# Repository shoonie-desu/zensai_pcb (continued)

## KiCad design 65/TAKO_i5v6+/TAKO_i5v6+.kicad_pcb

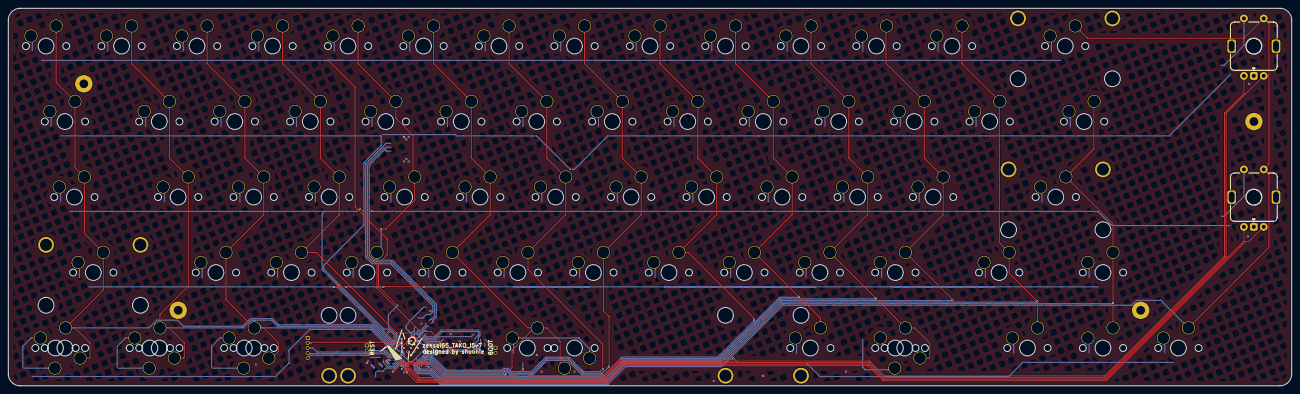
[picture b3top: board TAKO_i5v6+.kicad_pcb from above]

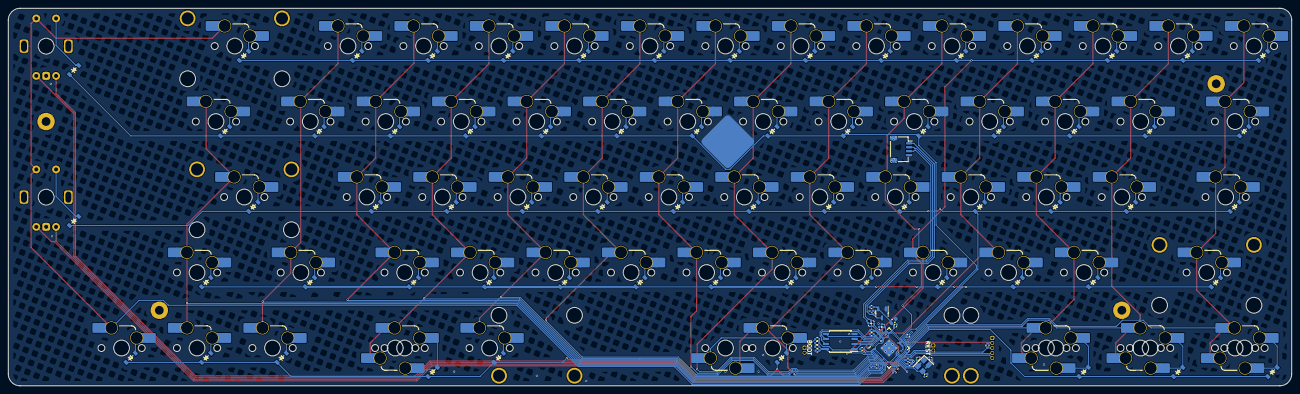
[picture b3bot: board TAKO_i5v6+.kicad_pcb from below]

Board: 2 copper layers, 323.8 x 95.2 mm, 177 parts (163 on the bottom side), 111 nets.

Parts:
C1, C2, C4, C6, C12: 1u; C_0402_1005Metric
C3: 10u; C_0603_1608Metric
C5, C7, C8, C9, C13, C14, C15, C16: 100n; C_0402_1005Metric
C10, C11: 22p; C_0402_1005Metric
D1, D2, D3, D4, D5, D6, D7, D8, D9, D10, D11, D12, D13, D15, D17, D18, D19, D20, D21, D22, D23, D24, D25, D26, D27, D28, D29, D30, D32, D34, D35, D36, D37, D38, D39, D40, D41, D42, D43, D44, D45, D47, D48, D50, D52, D53, D54, D55, D56, D57, D58, D59, D60, D61, D62, D63, D64, D66, D68, D70, D72, D74, D75, D76, D77: D_Small; D_SOD-123_CLEAN
H1, H2, H3, H4: MountingHole_Pad; MountingHole_2.2mm_M2_Pad
H5: info
H7: MountingHole_Pad; MountingHole_6mm_Pad
J1: ZX-SH1.0-4PWT; JST_SH_SM04B-SRSS-TB_1x04-1MP_P1.00mm_Horizontal
J3: Conn_01x05; PinHeader_1x05_P1.27mm_Vertical
R3, R8, R9: 5.1k; R_0402_1005Metric
R4, R5: 27; R_0402_1005Metric
R6, R7: 1k; R_0402_1005Metric
S15, S47, S50: MX_stab; STAB_MX_P_2u
S70: MX_stab; STAB_MX_P_6.25u
S71: MX_stab; STAB_MX_P_7u
SW1, SW2, SW3, SW4, SW5, SW6, SW7, SW8, SW9, SW10, SW11, SW12, SW13, SW15, SW17, SW18, SW19, SW20, SW21, SW22, SW23, SW24, SW25, SW26, SW27, SW28, SW29, SW30, SW34, SW35, SW36, SW37, SW38, SW39, SW40, SW41, SW42, SW43, SW44, SW45, SW47, SW50, SW52, SW53, SW54, SW55, SW56, SW57, SW58, SW59, SW60, SW61, SW62, SW63, SW64, SW65, SW66, SW67, SW68, SW69, SW70, SW71, SW72, SW73, SW74, SW75, SW76, SW77: SW_MX_HS_S; SW_MX_HS_S_CPG151101S11_1u
SW32, SW48: RotaryEncoder_Switch; ROT_Alps_EC11E-Switch
SW78: SW_RESET; PinHeader_1x02_P1.27mm_Vertical
SW79: SW_BOOTSEL; PinHeader_1x02_P1.27mm_Vertical
U1: RP2040; QFN-56-1EP_7x7mm_P0.4mm_EP3.2x3.2mm
U2: XC6206PxxxMR; SOT-23-3
U4: W25Q128JVS; SOIC-8_5.23x5.23mm_P1.27mm
Y1: Crystal_GND24; Crystal_SMD_3225-4Pin_3.2x2.5mm

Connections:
+1V1: C4.1, C5.1, C13.1, U1.23 (DVDD), U1.45 (VREG_VOUT), U1.50 (DVDD)
+3V3: C2.1, C3.1, C6.1, C7.1, C8.1, C9.1, C12.1, C14.1, C15.1, C16.1, J3.2, R3.2, R9.2, U1.1 (IOVDD), U1.10 (IOVDD), U1.22 (IOVDD), U1.33 (IOVDD), U1.42 (IOVDD), U1.43 (ADC_AVDD), U1.44 (VREG_IN), U1.48 (USB_VDD), U1.49 (IOVDD), U2.2 (VO), U4.8 (VCC)
+5V: C1.1, J1.1, U2.3 (VI)
COL0: SW1.2, SW17.2, SW34.2, SW50.2, SW64.2, SW65.1, U1.30 (GPIO19)
COL1: SW2.2, SW18.2, SW35.2, SW66.2, SW67.1, U1.29 (GPIO18)
COL2: SW3.2, SW19.2, SW36.2, SW52.2, SW68.2, SW69.1, U1.28 (GPIO17)
COL3: SW4.2, SW20.2, SW37.2, SW53.2, U1.2 (GPIO0)
COL4: SW5.2, SW21.2, SW38.2, SW54.2, U1.3 (GPIO1)
COL5: SW6.2, SW22.2, SW39.2, SW55.2, SW70.2, SW71.2, U1.7 (GPIO5)
COL6: SW7.2, SW23.2, SW40.2, SW56.2, U1.4 (GPIO2)
COL7: SW8.2, SW24.2, SW41.2, SW57.2, U1.5 (GPIO3)
COL8: SW9.2, SW25.2, SW42.2, SW58.2, U1.6 (GPIO4)
COL9: SW10.2, SW26.2, SW43.2, SW59.2, SW72.2, U1.8 (GPIO6)
COL10: SW11.2, SW27.2, SW44.2, SW60.2, SW73.2, SW74.1, U1.9 (GPIO7)
COL11: SW12.2, SW28.2, SW45.2, SW61.2, U1.11 (GPIO8)
COL12: SW13.2, SW29.2, SW62.2, SW75.2, U1.12 (GPIO9)
COL13: SW30.2, SW47.2, SW63.2, SW76.2, U1.13 (GPIO10)
COL14: SW15.2, SW32.S1, SW48.S1, SW77.2, U1.14 (GPIO11)
D+: J1.3, R4.1
D-: J1.2, R5.1
GND: C1.2, C2.2, C3.2, C4.2, C5.2, C6.2, C7.2, C8.2, C9.2, C10.1, C11.1, C12.2, C13.2, C14.2, C15.2, C16.2, H1.1, H2.1, H3.1, H4.1, H7.1, J1.4, J1.MP (MountPin), J3.1, SW32.C, SW32.MP, SW48.C, SW48.MP, SW78.1, SW79.1, U1.19 (TESTEN), U1.57 (GND), U2.1 (GND), U4.4 (GND), Y1.2, Y1.4
unnamed: C11.2, R6.1, Y1.1
unnamed: D1.2 (A), SW1.1
unnamed: D2.2 (A), SW2.1
unnamed: D3.2 (A), SW3.1
unnamed: D4.2 (A), SW4.1
unnamed: D5.2 (A), SW5.1
unnamed: D6.2 (A), SW6.1
unnamed: D7.2 (A), SW7.1
unnamed: D8.2 (A), SW8.1
unnamed: D9.2 (A), SW9.1
unnamed: D10.2 (A), SW10.1
unnamed: D11.2 (A), SW11.1
unnamed: D12.2 (A), SW12.1
unnamed: D13.2 (A), SW13.1
unnamed: D15.2 (A), SW15.1
unnamed: D17.2 (A), SW17.1
unnamed: D18.2 (A), SW18.1
unnamed: D19.2 (A), SW19.1
unnamed: D20.2 (A), SW20.1
unnamed: D21.2 (A), SW21.1
unnamed: D22.2 (A), SW22.1
unnamed: D23.2 (A), SW23.1
unnamed: D24.2 (A), SW24.1
unnamed: D25.2 (A), SW25.1
unnamed: D26.2 (A), SW26.1
unnamed: D27.2 (A), SW27.1
unnamed: D28.2 (A), SW28.1
unnamed: D29.2 (A), SW29.1
unnamed: D30.2 (A), SW30.1
unnamed: D32.2 (A), SW32.S2
unnamed: D34.2 (A), SW34.1
unnamed: D35.2 (A), SW35.1
unnamed: D36.2 (A), SW36.1
unnamed: D37.2 (A), SW37.1
unnamed: D38.2 (A), SW38.1
unnamed: D39.2 (A), SW39.1
unnamed: D40.2 (A), SW40.1
unnamed: D41.2 (A), SW41.1
unnamed: D42.2 (A), SW42.1
unnamed: D43.2 (A), SW43.1
unnamed: D44.2 (A), SW44.1
unnamed: D45.2 (A), SW45.1
unnamed: D47.2 (A), SW47.1
unnamed: D48.2 (A), SW48.S2
unnamed: D50.2 (A), SW50.1
unnamed: D52.2 (A), SW52.1
unnamed: D53.2 (A), SW53.1
unnamed: D54.2 (A), SW54.1
unnamed: D55.2 (A), SW55.1
unnamed: D56.2 (A), SW56.1
unnamed: D57.2 (A), SW57.1
unnamed: D58.2 (A), SW58.1
unnamed: D59.2 (A), SW59.1
unnamed: D60.2 (A), SW60.1
unnamed: D61.2 (A), SW61.1
unnamed: D62.2 (A), SW62.1
unnamed: D63.2 (A), SW63.1
unnamed: D64.2 (A), SW64.1, SW65.2
unnamed: D66.2 (A), SW66.1, SW67.2
unnamed: D68.2 (A), SW68.1, SW69.2
unnamed: D70.2 (A), SW70.1, SW71.1
unnamed: D72.2 (A), SW72.1
unnamed: D74.2 (A), SW73.1, SW74.2
unnamed: D75.2 (A), SW75.1
unnamed: D76.2 (A), SW76.1
unnamed: D77.2 (A), SW77.1
unnamed: R7.1, SW79.2
unnamed: R8.2, R9.1
unnamed: R5.2, U1.46 (USB_DM)
unnamed: R4.2, U1.47 (USB_DP)
QSPI_SCLK: U1.52 (QSPI_SCLK), U4.6 (CLK)
QSPI_SD0: U1.53 (QSPI_SD0), U4.5 (DI(IO0))
QSPI_SD1: U1.55 (QSPI_SD1), U4.2 (DO(IO1))
QSPI_SD2: U1.54 (QSPI_SD2), U4.3 (IO2)
QSPI_SD3: U1.51 (QSPI_SD3), U4.7 (IO3)
QSPI_SS: R7.2, R8.1, U1.56 (QSPI_SS), U4.1 (~CS)
RESET: J3.3, R3.1, SW78.2, U1.26 (RUN)
ROW0: D1.1 (K), D2.1 (K), D3.1 (K), D4.1 (K), D5.1 (K), D6.1 (K), D7.1 (K), D8.1 (K), D9.1 (K), D10.1 (K), D11.1 (K), D12.1 (K), D13.1 (K), D15.1 (K), U1.35 (GPIO23)
ROW1: D17.1 (K), D18.1 (K), D19.1 (K), D20.1 (K), D21.1 (K), D22.1 (K), D23.1 (K), D24.1 (K), D25.1 (K), D26.1 (K), D27.1 (K), D28.1 (K), D29.1 (K), D30.1 (K), D32.1 (K), U1.34 (GPIO22)
ROW2: D34.1 (K), D35.1 (K), D36.1 (K), D37.1 (K), D38.1 (K), D39.1 (K), D40.1 (K), D41.1 (K), D42.1 (K), D43.1 (K), D44.1 (K), D45.1 (K), D47.1 (K), D48.1 (K), U1.32 (GPIO21)
ROW3: D50.1 (K), D52.1 (K), D53.1 (K), D54.1 (K), D55.1 (K), D56.1 (K), D57.1 (K), D58.1 (K), D59.1 (K), D60.1 (K), D61.1 (K), D62.1 (K), D63.1 (K), U1.31 (GPIO20)
ROW4: D64.1 (K), D66.1 (K), D68.1 (K), D70.1 (K), D72.1 (K), D74.1 (K), D75.1 (K), D76.1 (K), D77.1 (K), U1.27 (GPIO16)
SW32A: SW32.A, U1.18 (GPIO15)
SW32B: SW32.B, U1.17 (GPIO14)
SW48A: SW48.A, U1.16 (GPIO13)
SW48B: SW48.B, U1.15 (GPIO12)
SWCLK: J3.5, U1.24 (SWCLK)
SWD: J3.4, U1.25 (SWD)
XIN: C10.2, U1.20 (XIN), Y1.3
XOUT: R6.2, U1.21 (XOUT)

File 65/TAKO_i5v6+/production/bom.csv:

Designator,Footprint,Quantity,Value,LCSC Part #
"C1, C12, C2, C4, C6",0402,5,1u,
"C10, C11",0402,2,22p,
"C13, C14, C15, C16, C5, C7, C8, C9",0402,8,100n,
C3,0603,1,10u,
"D1, D10, D11, D12, D13, D15, D17, D18, D19, D2, D20, D21, D22, D23, D24, D25, D26, D27, D28, D29, D3, D31, D32, D34, D35, D36, D37, D38, D39, D4, D40, D41, D42, D43, D44, D45, D46, D48, D5, D50, D52, D53, D54, D55, D56, D57, D58, D59, D6, D60, D61, D62, D63, D64, D66, D68, D7, D70, D72, D75, D76, D77, D8, D9",D_SOD-123_CLEAN,64,D_Small,
"H1, H2, H3, H4",MountingHole_2.2mm_M2_Pad,4,MountingHole_Pad,
H5,info,1,info,
H7,MountingHole_6mm_Pad,1,MountingHole_Pad,
J1,JST_SH_SM04B-SRSS-TB_1x04-1MP_P1.00mm_Horizontal,1,ZX-SH1.0-4PWT,
J3,PinHeader_1x05_P1.27mm_Vertical,1,Conn_01x05,
"R3, R8, R9",0402,3,5.1k,
"R4, R5",0402,2,27,
"R6, R7",0402,2,1k,
"S15, S47, S50",STAB_MX_P_2u,3,MX_stab,
S70,STAB_MX_P_6.25u,1,MX_stab,
S71,STAB_MX_P_7u,1,MX_stab,
"SW1, SW10, SW11, SW12, SW13, SW15, SW17, SW18, SW19, SW2, SW20, SW21, SW22, SW23, SW24, SW25, SW26, SW27, SW28, SW29, SW3, SW30, SW34, SW35, SW36, SW37, SW38, SW39, SW4, SW40, SW41, SW42, SW43, SW44, SW45, SW47, SW5, SW50, SW52, SW53, SW54, SW55, SW56, SW57, SW58, SW59, SW6, SW60, SW61, SW62, SW63, SW64, SW65, SW66, SW67, SW68, SW69, SW7, SW70, SW71, SW72, SW73, SW74, SW75, SW76, SW77, SW8, SW9",SW_MX_HS_S_CPG151101S11_1u,68,MX_SW_solder,
"SW32, SW48",ROT_Alps_EC11E-Switch,2,RotaryEncoder_Switch,
SW78,PinHeader_1x02_P1.27mm_Vertical,1,SW_RESET,
SW79,PinHeader_1x02_P1.27mm_Vertical,1,SW_BOOTSEL,
U1,QFN-56-1EP_7x7mm_P0.4mm_EP3.2x3.2mm,1,RP2040,
U2,SOT-23-3,1,XC6206PxxxMR,
U4,SOIC-8_5.23x5.23mm_P1.27mm,1,W25Q128JVS,
Y1,Crystal_SMD_3225-4Pin_3.2x2.5mm,1,Crystal_GND24,

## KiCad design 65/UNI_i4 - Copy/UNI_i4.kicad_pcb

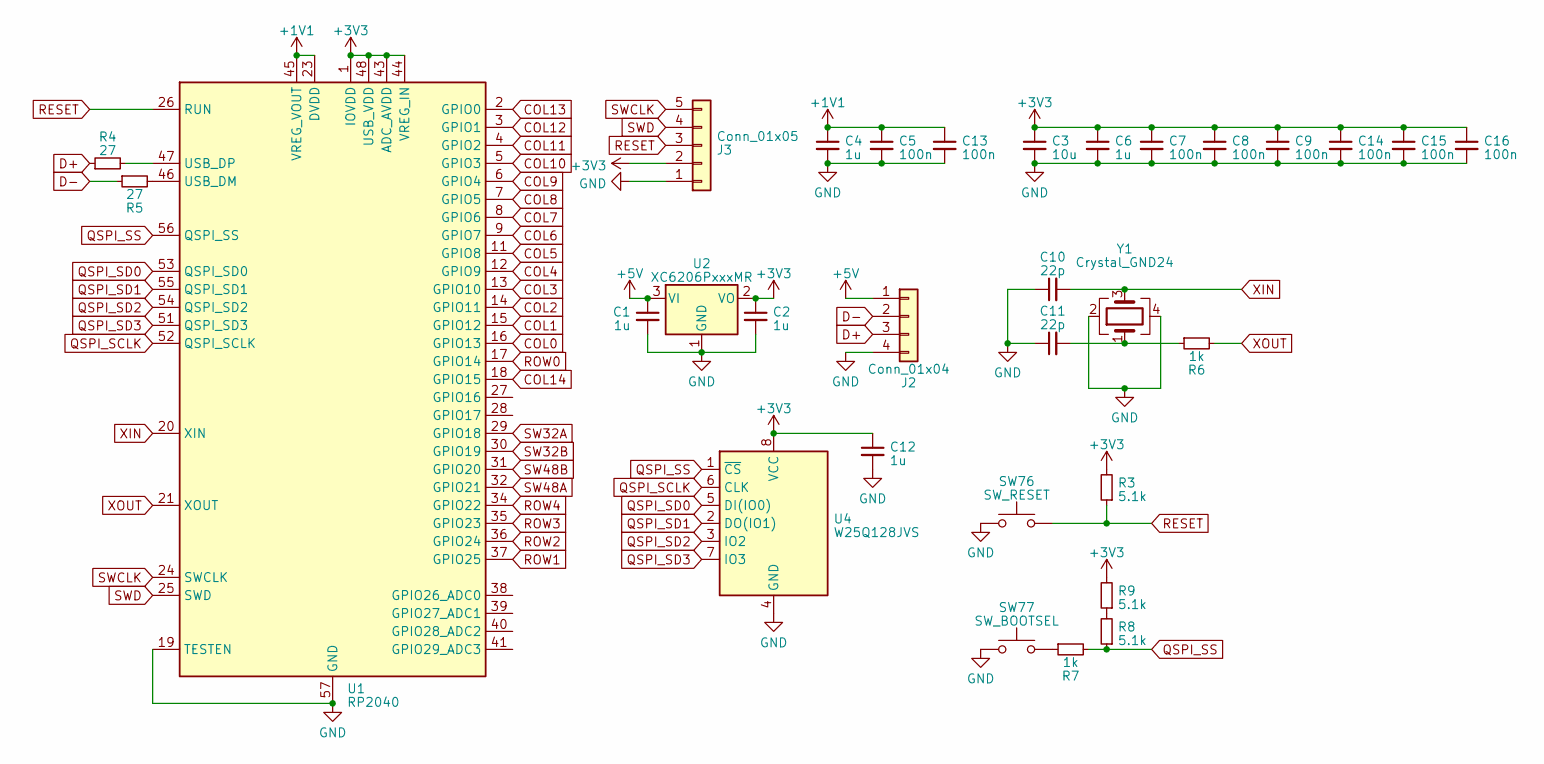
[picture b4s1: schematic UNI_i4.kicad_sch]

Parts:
C1, C2, C4, C6, C12: 1u; C_0402_1005Metric
C3: 10u; C_0603_1608Metric
C5, C7, C8, C9, C13, C14, C15, C16: 100n; C_0402_1005Metric
C10, C11: 22p; C_0402_1005Metric
J2: Conn_01x04; Molex_Pico-EZmate_78171-0004_1x04-1MP_P1.20mm_Vertical
J3: Conn_01x05; PinHeader_1x05_P2.54mm_Vertical
R3, R8, R9: 5.1k; R_0402_1005Metric
R4, R5: 27; R_0402_1005Metric
R6, R7: 1k; R_0402_1005Metric
SW76: SW_RESET; PinHeader_1x02_P1.27mm_Vertical
SW77: SW_BOOTSEL; PinHeader_1x02_P1.27mm_Vertical
U1: RP2040; QFN-56-1EP_7x7mm_P0.4mm_EP3.2x3.2mm
U2: XC6206PxxxMR; SOT-23-3
U4: W25Q128JVS; SOIC-8_5.23x5.23mm_P1.27mm
Y1: Crystal_GND24; Crystal_SMD_3225-4Pin_3.2x2.5mm

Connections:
+1V1: C4.1, C5.1, C13.1, U1.23 (DVDD), U1.45 (VREG_VOUT), U1.50 (DVDD)
+3V3: C2.1, C3.1, C6.1, C7.1, C8.1, C9.1, C12.1, C14.1, C15.1, C16.1, J3.2, R3.2, R9.2, U1.1 (IOVDD), U1.10 (IOVDD), U1.22 (IOVDD), U1.33 (IOVDD), U1.42 (IOVDD), U1.43 (ADC_AVDD), U1.44 (VREG_IN), U1.48 (USB_VDD), U1.49 (IOVDD), U2.2 (VO), U4.8 (VCC)
+5V: C1.1, J2.1, U2.3 (VI)
D+: J2.3, R4.1
D-: J2.2, R5.1
GND: C1.2, C2.2, C3.2, C4.2, C5.2, C6.2, C7.2, C8.2, C9.2, C10.1, C11.1, C12.2, C13.2, C14.2, C15.2, C16.2, J2.4, J3.1, SW76.1, SW77.1, U1.19 (TESTEN), U1.57 (GND), U2.1 (GND), U4.4 (GND), Y1.2, Y1.4
unnamed: C11.2, R6.1, Y1.1
unnamed 7: U1.2 (GPIO0); also elsewhere on the board
unnamed 8: U1.3 (GPIO1); also elsewhere on the board
unnamed 9: U1.4 (GPIO2); also elsewhere on the board
unnamed 10: U1.5 (GPIO3); also elsewhere on the board
unnamed 11: U1.6 (GPIO4); also elsewhere on the board
unnamed 12: U1.7 (GPIO5); also elsewhere on the board
unnamed 13: U1.8 (GPIO6); also elsewhere on the board
unnamed 14: U1.9 (GPIO7); also elsewhere on the board
unnamed 15: U1.11 (GPIO8); also elsewhere on the board
unnamed 16: U1.12 (GPIO9); also elsewhere on the board
unnamed 17: U1.13 (GPIO10); also elsewhere on the board
unnamed 18: U1.14 (GPIO11); also elsewhere on the board
unnamed 19: U1.15 (GPIO12); also elsewhere on the board
unnamed 20: U1.16 (GPIO13); also elsewhere on the board
unnamed 21: U1.17 (GPIO14); also elsewhere on the board
unnamed 22: U1.18 (GPIO15); also elsewhere on the board
unnamed 23: U1.27 (GPIO16); also elsewhere on the board
unnamed 24: U1.28 (GPIO17); also elsewhere on the board
unnamed 25: U1.29 (GPIO18); also elsewhere on the board
unnamed 26: U1.30 (GPIO19); also elsewhere on the board
unnamed 27: U1.31 (GPIO20); also elsewhere on the board
unnamed 28: U1.32 (GPIO21); also elsewhere on the board
unnamed 29: U1.34 (GPIO22); also elsewhere on the board
unnamed 30: U1.35 (GPIO23); also elsewhere on the board
unnamed 31: U1.36 (GPIO24); also elsewhere on the board
unnamed 32: U1.37 (GPIO25); also elsewhere on the board
unnamed 33: U1.38 (GPIO26_ADC0); also elsewhere on the board
unnamed 34: U1.39 (GPIO27_ADC1); also elsewhere on the board
unnamed 35: U1.40 (GPIO28_ADC2); also elsewhere on the board
unnamed 36: U1.41 (GPIO29_ADC3); also elsewhere on the board
unnamed: R7.1, SW77.2
unnamed: R8.2, R9.1
unnamed: R5.2, U1.46 (USB_DM)
unnamed: R4.2, U1.47 (USB_DP)
QSPI_SCLK: U1.52 (QSPI_SCLK), U4.6 (CLK)
QSPI_SD0: U1.53 (QSPI_SD0), U4.5 (DI(IO0))
QSPI_SD1: U1.55 (QSPI_SD1), U4.2 (DO(IO1))
QSPI_SD2: U1.54 (QSPI_SD2), U4.3 (IO2)
QSPI_SD3: U1.51 (QSPI_SD3), U4.7 (IO3)
QSPI_SS: R7.2, R8.1, U1.56 (QSPI_SS), U4.1 (~CS)
RESET: J3.3, R3.1, SW76.2, U1.26 (RUN)
SWCLK: J3.5, U1.24 (SWCLK)
SWD: J3.4, U1.25 (SWD)
XIN: C10.2, U1.20 (XIN), Y1.3
XOUT: R6.2, U1.21 (XOUT)

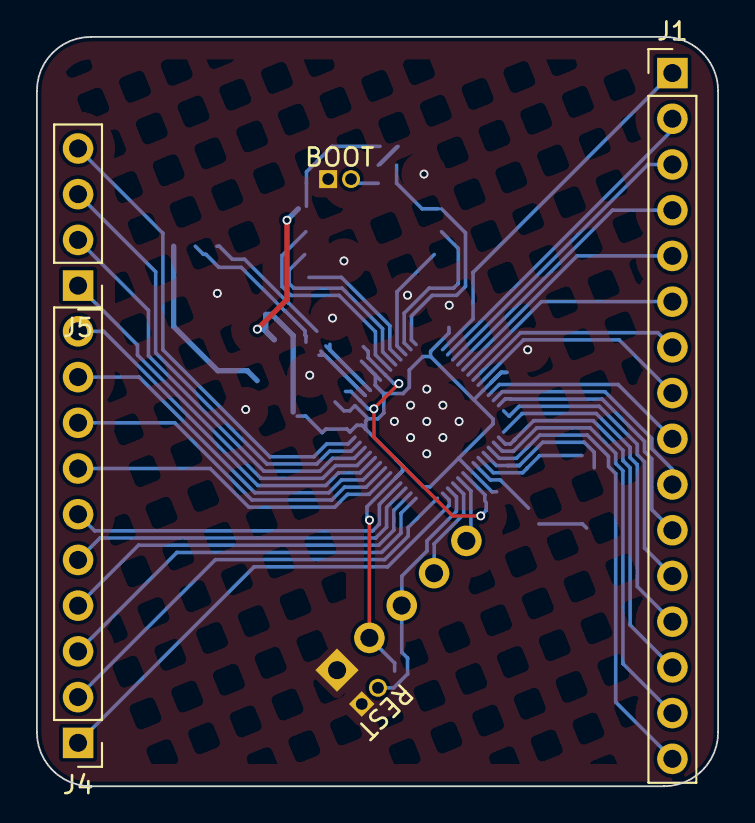
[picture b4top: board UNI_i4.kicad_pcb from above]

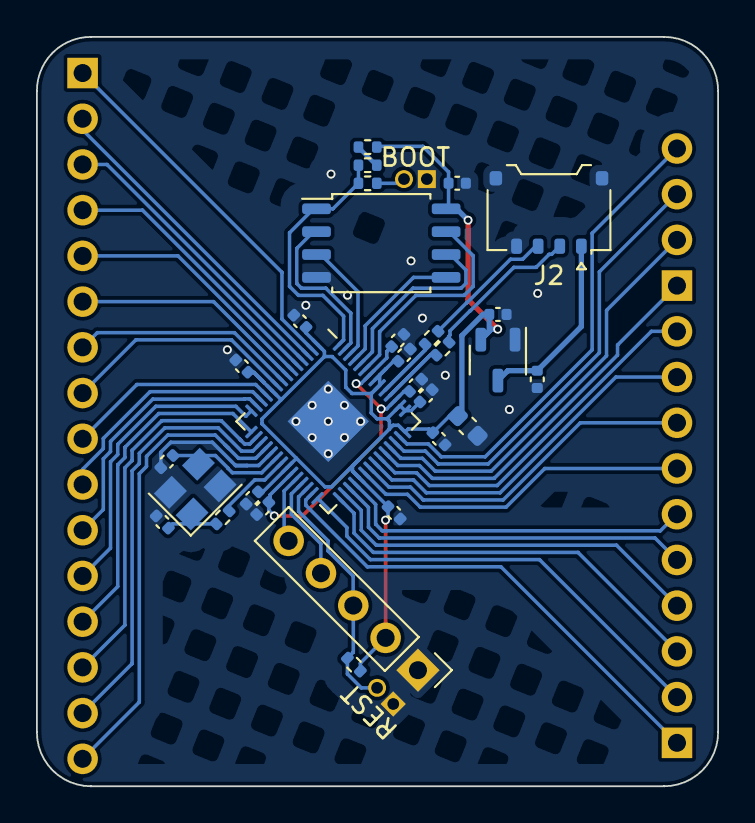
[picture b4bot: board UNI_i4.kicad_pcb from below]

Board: 2 copper layers, 37.8 x 41.6 mm, 34 parts (31 on the bottom side), 52 nets.

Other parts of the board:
J1: Conn_01x16; PinHeader_1x16_P2.54mm_Vertical
J4: Conn_01x10; PinHeader_1x10_P2.54mm_Vertical
J5: Conn_01x04; PinHeader_1x04_P2.54mm_Vertical

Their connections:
unnamed 7: J1.1; also elsewhere on the board
unnamed 8: J1.2; also elsewhere on the board
unnamed 9: J1.3; also elsewhere on the board
unnamed 10: J1.4; also elsewhere on the board
unnamed 11: J1.5; also elsewhere on the board
unnamed 12: J1.6; also elsewhere on the board
unnamed 13: J1.7; also elsewhere on the board
unnamed 14: J1.8; also elsewhere on the board
unnamed 15: J1.9; also elsewhere on the board
unnamed 16: J1.10; also elsewhere on the board
unnamed 17: J1.11; also elsewhere on the board
unnamed 18: J1.12; also elsewhere on the board
unnamed 19: J1.13; also elsewhere on the board
unnamed 20: J1.14; also elsewhere on the board
unnamed 21: J1.15; also elsewhere on the board
unnamed 22: J1.16; also elsewhere on the board
unnamed 23: J4.1; also elsewhere on the board
unnamed 24: J4.2; also elsewhere on the board
unnamed 25: J4.3; also elsewhere on the board
unnamed 26: J4.4; also elsewhere on the board
unnamed 27: J4.5; also elsewhere on the board
unnamed 28: J4.6; also elsewhere on the board
unnamed 29: J4.7; also elsewhere on the board
unnamed 30: J4.8; also elsewhere on the board
unnamed 31: J4.9; also elsewhere on the board
unnamed 32: J4.10; also elsewhere on the board
unnamed 33: J5.1; also elsewhere on the board
unnamed 34: J5.2; also elsewhere on the board
unnamed 35: J5.3; also elsewhere on the board
unnamed 36: J5.4; also elsewhere on the board

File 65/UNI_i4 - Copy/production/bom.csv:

Designator,Footprint,Quantity,Value,LCSC Part #
"C1, C12, C2, C4, C6",0402,5,1u,
"C10, C11",0402,2,22p,
"C13, C14, C15, C16, C5, C7, C8, C9",0402,8,100n,
C3,0603,1,10u,
J1,PinHeader_1x16_P2.54mm_Vertical,1,Conn_01x16,
J2,Molex_Pico-EZmate_78171-0004_1x04-1MP_P1.20mm_Vertical,1,Conn_01x04,
J3,PinHeader_1x05_P2.54mm_Vertical,1,Conn_01x05,
J4,PinHeader_1x10_P2.54mm_Vertical,1,Conn_01x10,
J5,PinHeader_1x04_P2.54mm_Vertical,1,Conn_01x04,
"R3, R8, R9",0402,3,5.1k,
"R4, R5",0402,2,27,
"R6, R7",0402,2,1k,
SW76,PinHeader_1x02_P1.27mm_Vertical,1,SW_RESET,
SW77,PinHeader_1x02_P1.27mm_Vertical,1,SW_BOOTSEL,
U1,QFN-56-1EP_7x7mm_P0.4mm_EP3.2x3.2mm,1,RP2040,
U2,SOT-23-3,1,XC6206PxxxMR,
U4,SOIC-8_5.23x5.23mm_P1.27mm,1,W25Q128JVS,
Y1,Crystal_SMD_3225-4Pin_3.2x2.5mm,1,Crystal_GND24,

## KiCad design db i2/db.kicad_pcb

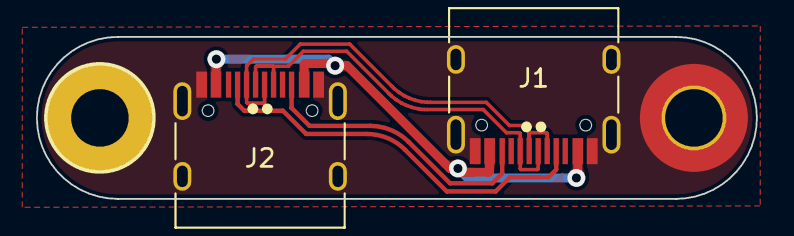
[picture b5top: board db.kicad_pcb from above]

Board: 2 copper layers, 40.0 x 9.0 mm, 4 parts (0 on the bottom side), 6 nets.

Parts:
H1: MountingHole; MountingHole_3.2mm_M3_DIN965_Pad_TopBottom
H2: MountingHole; MountingHole_3.2mm_M3_DIN965_Pad_TopOnly
J1, J2: USB_C_Receptacle_USB2.0; USB_C_Receptacle_HRO_TYPE-C-31-M-12

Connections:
D+: J1.A7 (D-), J1.B7 (D-), J2.A7 (D-), J2.B7 (D-)
D-: J1.A6 (D+), J1.B6 (D+), J2.A6 (D+), J2.B6 (D+)
GND: H1.1, H2.1, J1.A1 (GND), J1.A12 (GND), J1.B1 (GND), J1.B12 (GND), J1.S1 (SHIELD), J2.A1 (GND), J2.A12 (GND), J2.B1 (GND), J2.B12 (GND), J2.S1 (SHIELD)
unnamed: J1.A5 (CC1), J2.A5 (CC1)
unnamed: J1.B5 (CC2), J2.B5 (CC2)
VBUS: J1.A4 (VBUS), J1.A9 (VBUS), J1.B4 (VBUS), J1.B9 (VBUS), J2.A4 (VBUS), J2.A9 (VBUS), J2.B4 (VBUS), J2.B9 (VBUS)

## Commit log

2023-04-10 uni_i3
2023-04-13 moved files
2023-04-13 75unii1
2023-05-11 working on 60B uni
2023-05-15 working on tako i3
2023-05-15 UNI/TAKO i3 for production
2023-05-19 tako i3 changes
2023-06-07 created i4 with rp2040
2023-08-16 8/16
2023-09-24 65 v3
2023-09-30 added template
2023-11-09 uni tako icons
2024-01-15 i5v5
    split backspace
2024-01-20 i5v6
2024-01-21 v6 finalized
2025-03-08 i5v6 ported to tako
2025-03-08 i7_uni init
2025-03-10 i7_uni pause
2025-03-10 i8 start
2025-03-13 i8 development
2025-03-14 downgraded flash chip
2025-03-16 begin tako40_i8
2025-03-16 tako40_i8 drafted
2025-03-18 i8 iterating
2025-03-18 prying voltage regulator
2025-03-19 added rp2350 lib submodule
2025-04-19 chiffrei8v1 posting...
2025-07-08 version label
2025-07-10 curve tweaking
2025-07-10 i9 init
2025-07-10 NAMING SCHEME
2025-08-01 c8v2 stable
2025-09-06 finalized chiff c8v2
2025-09-12 c8v3 development
2025-09-22 finalizing c8v3_tako...
2025-09-28 c8v3_tako finalized
2025-12-06 c10 init
2026-01-24 c10 drafting
2026-01-25 tag connect routed
2026-01-29 begin matrix signaling
2026-05-18 c8v4
